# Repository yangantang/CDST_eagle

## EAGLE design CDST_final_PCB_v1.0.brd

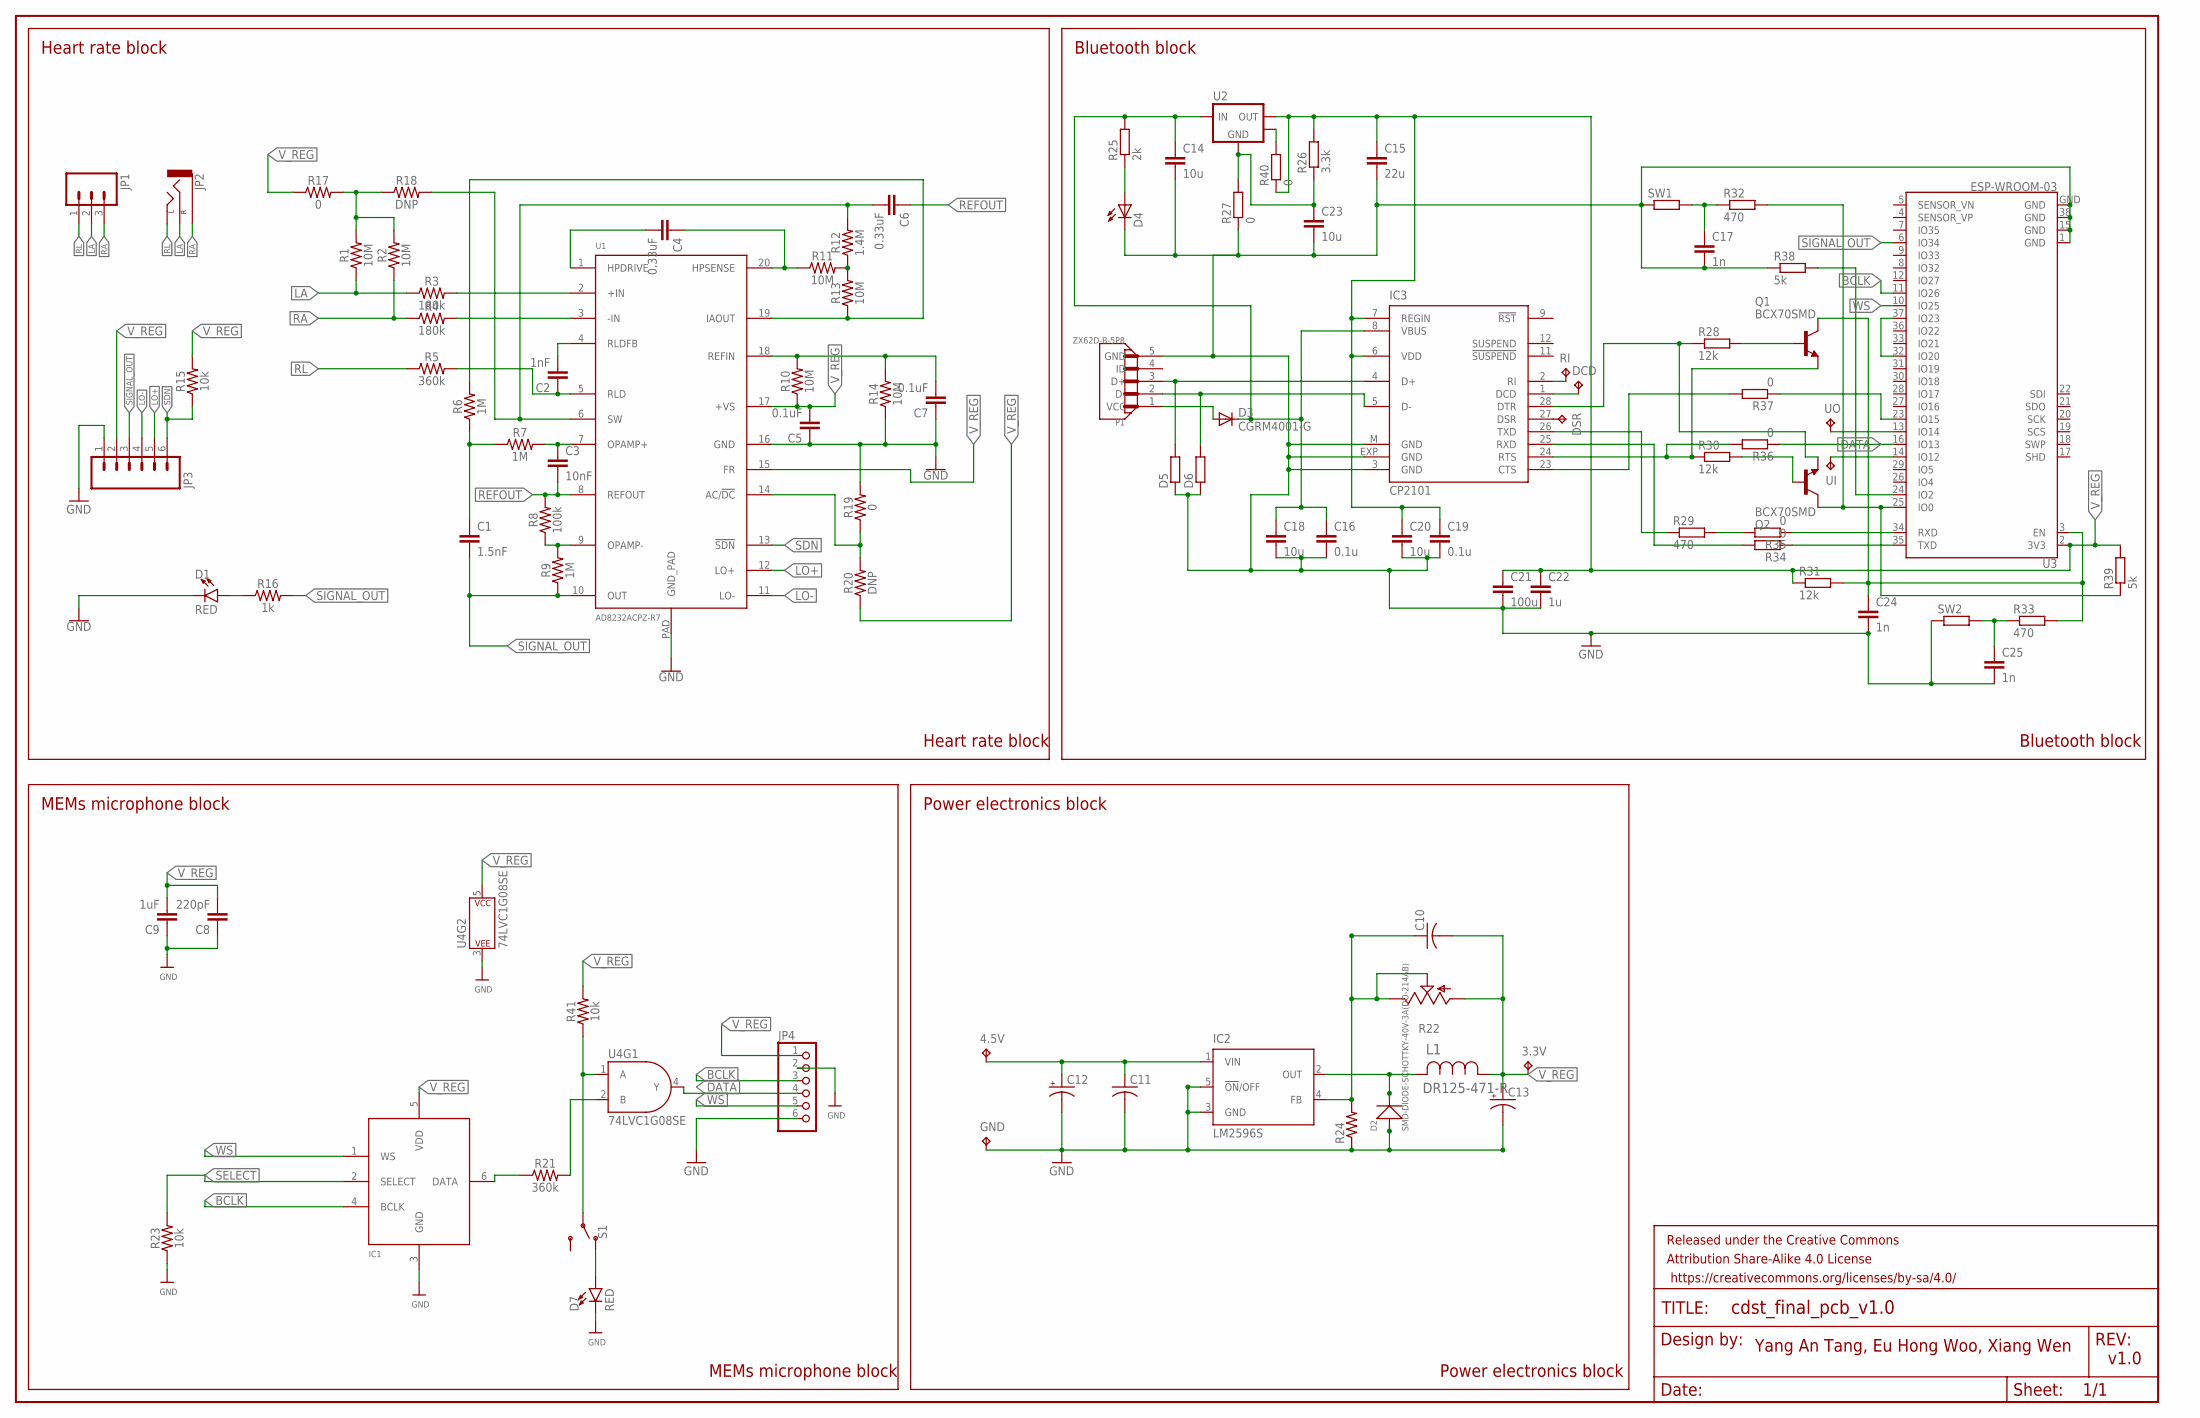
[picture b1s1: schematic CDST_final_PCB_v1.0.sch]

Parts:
3.3V, 4.5V: TPTP20SQ; TP20SQ
C1: 1.5nF; C1206
C2: 1nF; C1206
C3: 10nF; C1206
C4, C6: 0.33uF; C1206
C5, C7: 0.1uF; C1206
C8: 220pF; C1206
C9: 1uF; C1206
C10, C11: C-USC0402; C0402
C12, C13: CPOL-USSANYO_SMD_F8; SANYO-OSCON_SMD_F8
C14, C18, C20, C23: 10u; C1206
C15: 22u; C1206
C16, C19: 0.1u; C1206
C17, C24, C25: 1n; C1206
C21: 100u; C1206
C22: 1u; C1206
D1, D7: RED; LED-1206
D2: SMD-DIODE-SCHOTTKY-40V-3A(DO-214AB); DO-214AB
D3: CGRM4001-G; SOD-123_MINI-SMA
D4: LEDCHIPLED_0805; CHIPLED_0805
D5, D6: RR0402; R0402
DCD: TPB2,54; B2,54
DSR: TPB2,54; B2,54
FRAME1: FRAME-LEDGER; CREATIVE_COMMONS
GND: TPTP20SQ; TP20SQ
IC1: MIC_I2S_SPH0645; SPH0645LM4H
IC2: LM2596S; TO263-5
IC3: CP2101; MLP28
JP1: M03PTH; 1X03
JP2: AUDIO-JACKSMD2; AUDIO-JACK-3.5MM-SMD
JP3: M06SIP; 1X06
JP4: HEADER-1X6ROUND; 1X06_ROUND
L1: DR125-471-R; INDM125125X600N
P1: ZX62D-B-5P8; HRS_ZX62D-B-5P8
Q1, Q2: BCX70SMD; SOT23
R1, R2, R10, R11, R13, R14: 10M; 1206
R3, R4: 180k; 1206
R5, R21: 360k; 1206
R6, R7, R9: 1M; 1206
R8: 100k; 1206
R12: 1.4M; 1206
R15, R23, R41: 10k; 1206
R16: 1k; 1206
R17, R19: 0; 1206
R18, R20: DNP; 1206
R22: TRIM_US-RJ9W; RJ9W
R24: R-US_MELF0204W; MINI_MELF-0204W
R25: 2k; R1206
R26: 3.3k; R1206
R27, R34, R35, R36, R37, R40: 0; R1206
R28, R30, R31: 12k; R1206
R29, R32, R33: 470; R1206
R38, R39: 5k; R1206
RI: TPB2,54; B2,54
S1: SWITCH-SPDT-SMD-RIGHT-ANGLE; SWITCH_SPST_SMD_A
SW1, SW2: RR2010; R2010
U1: AD8232ACPZ-R7; LFCSP_20
U2: LM1117-SOT223; SOT-223-3
U3: ESP-WROOM-03
U4: 74LVC1G08SE; SOT23-5
UI: TPB1,27; B1,27
UO: TPB1,27; B1,27

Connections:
BCLK: IC1.4 (BCLK), JP4.3, U3.11 (IO26)
DATA: JP4.4, R36.1, U3.16 (IO13), U4.4 (Y)
DCD: DCD.TP, IC3.1 (DCD)
GND: C5.1, C7.1, C8.1, C9.1, C11.2, C12.-, C13.-, C14.2, C15.2, C16.2, C17.2, C18.2, C19.2, C20.2, C21.2, C22.2, C23.1, C23.2, C24.2, C25.2, D1.C, D2.1 (+), D4.C, D5.1, D6.1, D7.C, GND.TP, IC1.3 (GND), IC2.3 (GND), IC2.5 (!ON!/OFF), IC3.3 (GND), IC3.EXP (GND), IC3.M (GND), JP3.1, JP4.2, JP4.6, P1.5 (GND), R14.1, R19.2, R23.1, R24.1, R26.1, R27.1, R27.2, R38.1, SW1.1, SW2.1, U1.16 (GND), U1.PAD (GND_PAD), U2.1 (GND), U3.1 (GND), U3.15 (GND), U3.38 (GND), U3.GND, U4.3 (P$V-)
HEATSINK: R40.2, U2.4 (HEATSINK)
LA: JP1.2, JP2.RING (RIGHT), R1.1, R3.1
LO+: JP3.5, U1.12 (LO+)
LO-: JP3.4, U1.11 (LO-)
unnamed: C4.2, U1.1 (HPDRIVE)
unnamed: C4.1, R11.1, U1.20 (HPSENSE)
unnamed: R11.2, R12.1, R13.2
unnamed: C6.2, R12.2, R18.2, U1.6 (SW)
unnamed: C3.1, R7.2, U1.7 (OPAMP+)
unnamed: 4.5V.TP, C11.1, C12.+, IC2.1 (VIN)
unnamed: R6.2, R13.1, U1.19 (IAOUT)
unnamed: C1.1, R6.1, R7.1
unnamed: D4.A, R25.1
unnamed: IC1.6 (DATA), R21.1
unnamed: R8.1, R9.2, U1.9 (OPAMP-)
unnamed: C10.1, IC2.4 (FB), R22.E, R22.S, R24.2
unnamed: R3.2, U1.2 (+IN)
unnamed: R4.2, U1.3 (-IN)
unnamed: D1.A, R16.1
unnamed: R1.2, R2.2, R17.2, R18.1
unnamed: C2.2, U1.4 (RLDFB)
unnamed: C2.1, R5.2, U1.5 (RLD)
unnamed: C7.2, R10.2, R14.2, U1.18 (REFIN)
unnamed: C14.1, C16.1, C18.1, D3.C, IC3.8 (VBUS), R25.2, U2.3 (VIN)
unnamed: D2.2 (-), IC2.2 (OUT), L1.2
unnamed: R19.1, R20.2, U1.14 (AC/!DC)
unnamed: D5.2, IC3.4 (D+), P1.3 (D+)
unnamed: D6.2, IC3.5 (D-), P1.2 (D-)
unnamed: D3.A, P1.1 (VCC)
unnamed: Q1.1 (B), R28.2
unnamed: IC3.24 (RTS), Q1.2 (E), R30.1, R36.2
unnamed: IC3.28 (DTR), Q2.2 (E), R28.1
unnamed: C24.1, Q1.3 (C), R31.2, R33.2, U3.3 (EN)
unnamed: IC3.25 (RXD), R34.2
unnamed: IC3.26 (TXD), R29.1
unnamed: U3.13 (IO14), UO.TP
unnamed: U3.32 (IO20), U3.37 (IO23)
unnamed: C25.1, R33.1, SW2.2
unnamed: C17.1, R32.1, SW1.2
unnamed: Q2.3 (C), R32.2, R39.1, U3.25 (IO0)
unnamed: R38.2, U3.24 (IO2)
unnamed: R34.1, U3.35 (TXD)
unnamed: R29.2, R35.2
unnamed: R35.1, U3.34 (RXD)
unnamed: U3.14 (IO12), UI.TP
unnamed: IC3.23 (CTS), R37.2
unnamed: R37.1, U3.23 (IO15)
unnamed: Q2.1 (B), R30.2
unnamed: IC3.2 (RI), RI.TP
unnamed: DSR.TP, IC3.27 (DSR)
unnamed: D7.A, S1.1 (O)
unnamed: R21.2, U4.2 (B)
unnamed: R41.1, S1.2, U4.1 (A)
RA: JP1.3, JP2.SLEEVE, R2.1, R4.1
REFOUT: C3.2, C6.1, R8.2, U1.8 (REFOUT)
RL: JP1.1, JP2.TIP (LEFT), R5.1
SDN: JP3.6, R15.1, U1.13 (!SDN)
SELECT: IC1.2 (SELECT), R23.2
SIGNAL_OUT: C1.2, JP3.3, R9.1, R16.2, U1.10 (OUT), U3.6 (IO34)
V_REG: 3.3V.TP, C5.2, C8.2, C9.2, C10.2, C13.+, C15.1, C19.1, C20.1, C21.1, C22.1, IC1.5 (VDD), IC3.6 (VDD), IC3.7 (REGIN), JP3.2, JP4.1, L1.1, R10.1, R15.2, R17.1, R20.1, R22.A, R26.2, R31.1, R39.2, R40.1, R41.2, U1.15 (FR), U1.17 (+VS), U2.2 (VOUT), U3.2 (3V3), U4.5 (P$V+)
WS: IC1.1 (WS), JP4.5, U3.10 (IO25)

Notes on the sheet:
Yang An Tang, Eu Hong Woo, Xiang Wen
v1.0
Heart rate block
MEMs microphone block
Power electronics block
Bluetooth block

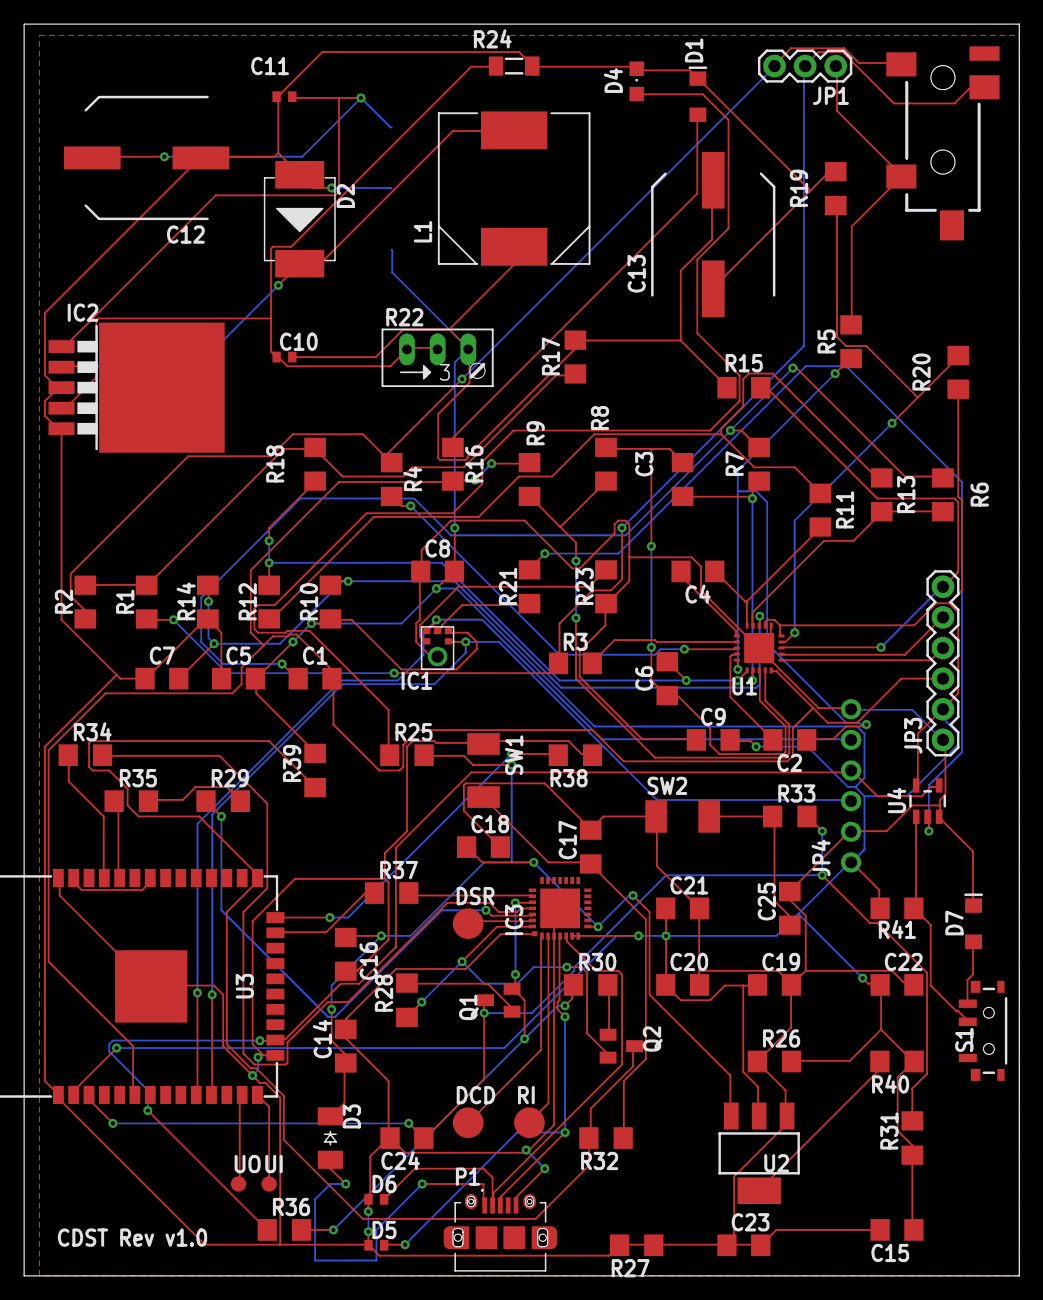
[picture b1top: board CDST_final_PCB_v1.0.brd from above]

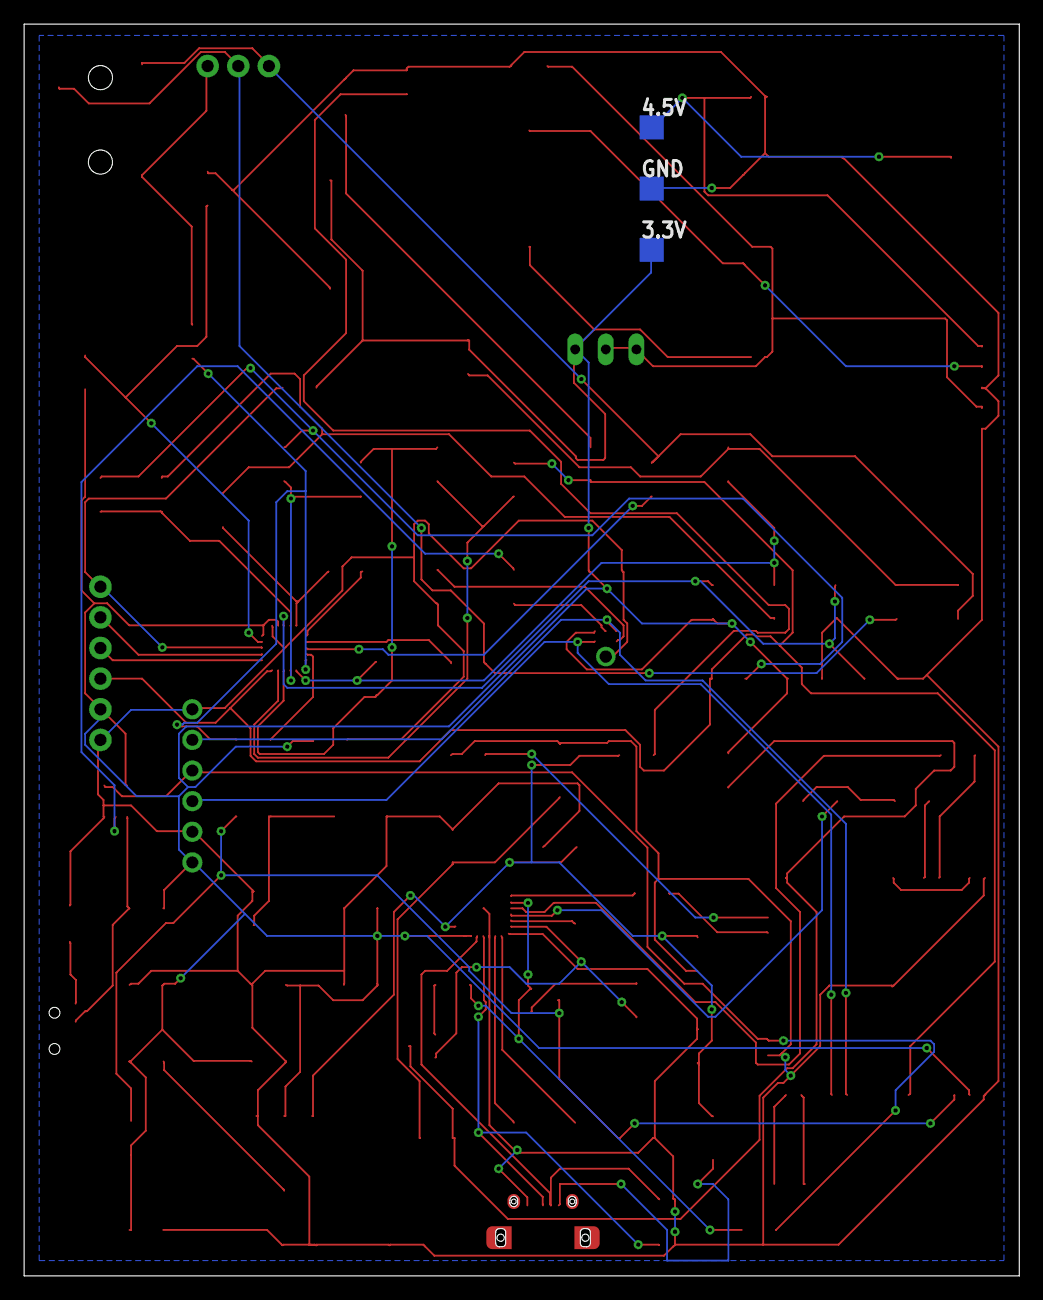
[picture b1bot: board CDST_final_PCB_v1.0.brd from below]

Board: 2 copper layers, 82.5 x 103.8 mm, 100 parts (3 on the bottom side), 65 nets.

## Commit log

2017-11-15 added power electronics
2017-11-15 fixed ERC errors
2017-11-15 added esp32
2017-11-15 Test pin added to ESP
2017-11-15 layout revision v0.1
2017-11-15 pcb layout done

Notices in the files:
parts and their libraries:
SparkFun-LED: Licensing: CC v3.0 Share-Alike You are welcome to use this library for commercial purposes.
microbuilder: This work is placed in the public domain, and may be freely used for commercial and non-commercial work with the following conditions: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
